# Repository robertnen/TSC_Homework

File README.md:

### Nenciu George-Robert 333CC

# TSC_Homework
## Schema pe scurt
<div align="center">
  
</div>
<br>

## Imaginea 3D 

<br>

# Conexiuni Hardware - Proiect ESP32-C6

## ESP32-C6-WROOM-1-N8 (Microcontroler Principal)
- Interfețe disponibile: SPI, I2C, UART, GPIO

---

## BME688 (Senzor Ambiental)
- Interfață: I2C  
- **Pini utilizați**:  
  - SDA → IO21  
  - SCL → IO22

---

## DS3231SN (Real-Time Clock)
- Interfață: I2C (partajat cu BME688)  
- **Pini utilizați**:  
  - SDA → IO21  
  - SCL → IO22  
  - INT_RTC → IO8  
  - 32KHZ → IO1  
  - RTC_RST → IO18

---

## Afișaj E-Ink (7.5 inch)
- Interfață: SPI  
- Rezoluție: 800 x 480 px  
- **Pini utilizați**:  
  - EPD_CS → IO10  
  - EPD_DC → IO5  
  - EPD_RST → IO23  
  - EPD_BUSY → IO3 *(partajat cu MISO)*  
  - MOSI, SCK *(partajate cu SD)*

---

## Modul SD Card
- Interfață: SPI  
- **Pini utilizați**:  
  - SS_SD → IO4  
  - MOSI → IO7  
  - MISO → IO2  
  - SCK → IO6

---

## Memorie Externă Flash (W25Q512JVEIQ, 64MB)
- Interfață: SPI  
- **Pini utilizați**:  
  - FLASH_CS → IO12  
  - MOSI, MISO, SCK *(partajate cu SD)*

---

## Interfață USB/SD
- Funcții: alimentare + date  
- **Pini utilizați**:  
  - USB_D+ → IO13  
  - USB_D- → IO12

---

## Butoane Boot și Reset
- **Pini utilizați**:  
  - IO/BOOT → IO9  
  - RESET → pin dedicat *(conform schemei)*

---

## Sistem de Alimentare și Management
- Baterie Li-Po: 3.7V, 2500mAh  
- **Module și pini**:
  - MCP73831 → încărcare prin USB-C  
  - MAX17048 → monitorizare baterie  
    - SDA → IO21  
    - SCL → IO22  
  - XC6220A331MR-G → 3.3V stabilizat

---

## Conector USB-C
- Funcții: alimentare principală și transfer de date  
- Protejat ESD

---

## Conector Qwiic / Stemma QT
- Interfață: I2C  
- **Pini utilizați**:
  - SDA → IO21  
  - SCL → IO22

<p>ESP32-C6 are un consum de energie optimizat pentru aplicații IoT. În modul activ, consumul variază în funcție de sarcină, dar poate fi redus semnificativ în modurile de repaus profund. De exemplu, în modul Deep Sleep, consumul poate fi de ordinul microamperilor, ceea ce permite o durată de viață extinsă a bateriei.</p>

### Notă privind erorile Airwire / Air Wire

În cadrul designului hardware, anumite erori de tip **Airwire** au fost acceptate intenționat în schema/PCB. Acestea reprezintă conexiuni logice nefinalizate în layout-ul plăcii, dar au fost tolerate în scopuri de testare, dezvoltare rapidă sau în situații unde conexiunile sunt realizate manual (ex: prin fire externe sau jumperi în faza de prototipare). 

Decizia de a le păstra a fost luată pentru a permite flexibilitate în modificări ulterioare și pentru a grăbi ciclul de iterație fără a compromite funcționalitatea de bază a sistemului.

## Alte considerații

<p>În proiectare, s-a ținut cont de recomandările din ghidul de design hardware pentru ESP32-C6 , asigurându-se că traseele PCB pentru interfața I2C sunt cât mai scurte și ecranate corespunzător pentru a minimiza interferențele. De asemenea, s-a acordat atenție alimentării corecte a senzorului BME680, conform specificațiilor acestuia.​

Pentru o integrare eficientă a componentelor și optimizarea performanței, s-au urmat recomandările din documentația oficială a ESP32-C6 și a componentelor asociate.</p>

| Componentă | Nr. bucăți | Nume material | Link către datasheet |
|---|---|---|---|
| EAGLE-LTSPICE_C0402 | 26 | Discrete Component | https://eu.mouser.com/datasheet/2/447/KEM_C1023_X7R_AUTO_SMD-3316698.pdf |
| ESP32_WROVER_AVX---SD0805S020S1R0_AVX_SD0805S020S1R0_0 | 2 | Discrete Component | https://eu.mouser.com/datasheet/2/40/AutoMLCCKAM-3216307.pdf |
| ESP32_WROVER_EAGLE-LTSPICE_R0402 | 22 | Discrete Component | https://eu.mouser.com/datasheet/2/54/cr-1858361.pdf |
| TP20R | 17 | Discrete Component | https://www.koaspeer.com/pdfs/RN73R.pdf |
| ESP32_WROVER_SPARKFUN-IC-POWER_SOT23-5 | 1 | Discrete Component | https://eu.mouser.com/datasheet/2/891/Espressif_Systems_ESP32_WROVER_E_L_0-3049094.pdf |
| ADAFRUIT_CHIP-LED0603 | 1 | Discrete Component | https://www.vishay.com/doc?82437 |
| ESP32_WROVER_BME680_PSON80P300X300X100-8N | 1 | Discrete Component | https://eu.mouser.com/datasheet/2/783/BST_BME680_DS001-1509608.pdf |
| ESP32C6_VARISTOR_CT/CN1812 | 1 | Discrete Component | https://product.tdk.com/system/files/dam/doc/product/protection/voltage/varistor_ctvs/data_sheet/75/db/ctvs_14/ct1210s14bautogx1.pdf |
| DIOC1608X36N | 6 | Discrete Component | https://eu.mouser.com/datasheet/2/802/1703143356438-3483895.pdf |
| SOT95P280X120-5N | 1 | Discrete Component | https://www.onsemi.com/PowerSolutions/product.do?id=MC74VHC1GT32P5T5G |
| CAPCP3225X100N | 1 | Discrete Component | https://eu.mouser.com/datasheet/2/18/2/CAP_CACFSBA1-3557832.pdf |
| RCL_CT3528 | 1 | Discrete Component | https://www.vishay.com/doc?20046 |
| ESP32_WROVER_SPARKFUN-DISCRETESEMI_SOT23-3 | 2 | Discrete Component | https://eu.mouser.com/datasheet/2/891/Espressif_Systems_ESP32_WROVER_E_L_0-3049094.pdf |
| SAMACSYS_PARTS_USB4110GFA | 1 | Discrete Component | https://eu.mouser.com/datasheet/2/837/GCT_USB4120-3159195.pdf |
| JST04_1MM_RA | 1 | Discrete Component | https://eu.mouser.com/datasheet/2/564/eCPT-3475515.pdf |
| SOIC127P1032X265-16N | 1 | Discrete Component | https://www.ti.com/lit/ug/sbou289/sbou289.pdf?ts=1664458800011&ref_url=https%253A%252F%252Fwww.ti.com%252Ftool%252FSURFACE-MOUNT-ADAPTER-EVM%253FkeyMatch%253D%2526tisearch%253Dsearch-everything%2526usecase%253Dhardware |
| XCVR_ESP32-C6-WROOM-1-N8 | 1 | Discrete Component | https://eu.mouser.com/datasheet/2/891/esp32_c6_datasheet_en-3304070.pdf |
| SOT95P280X145-6N | 1 | Discrete Component | https://eu.mouser.com/datasheet/2/414/DIV23-3532318.pdf |
| SOT95P280X125-5N | 1 | Discrete Component | https://eu.mouser.com/datasheet/2/414/DIV23-1551440.pdf |
| FH34SRJ24S05SH99 | 1 | Discrete Component | https://eu.mouser.com/datasheet/2/833/cherry_Rocker_SR_Round_EN-1275415.pdf |
| SON127P600X800X80-9N | 1 | Discrete Component | https://www.ti.com/lit/gpn/tps63710 |
| 16-soldermask | 1 | Steel | https://eu.mouser.com/datasheet/2/58/BPS-DAT-(BB3U)-Datasheet-1282462.pdf |

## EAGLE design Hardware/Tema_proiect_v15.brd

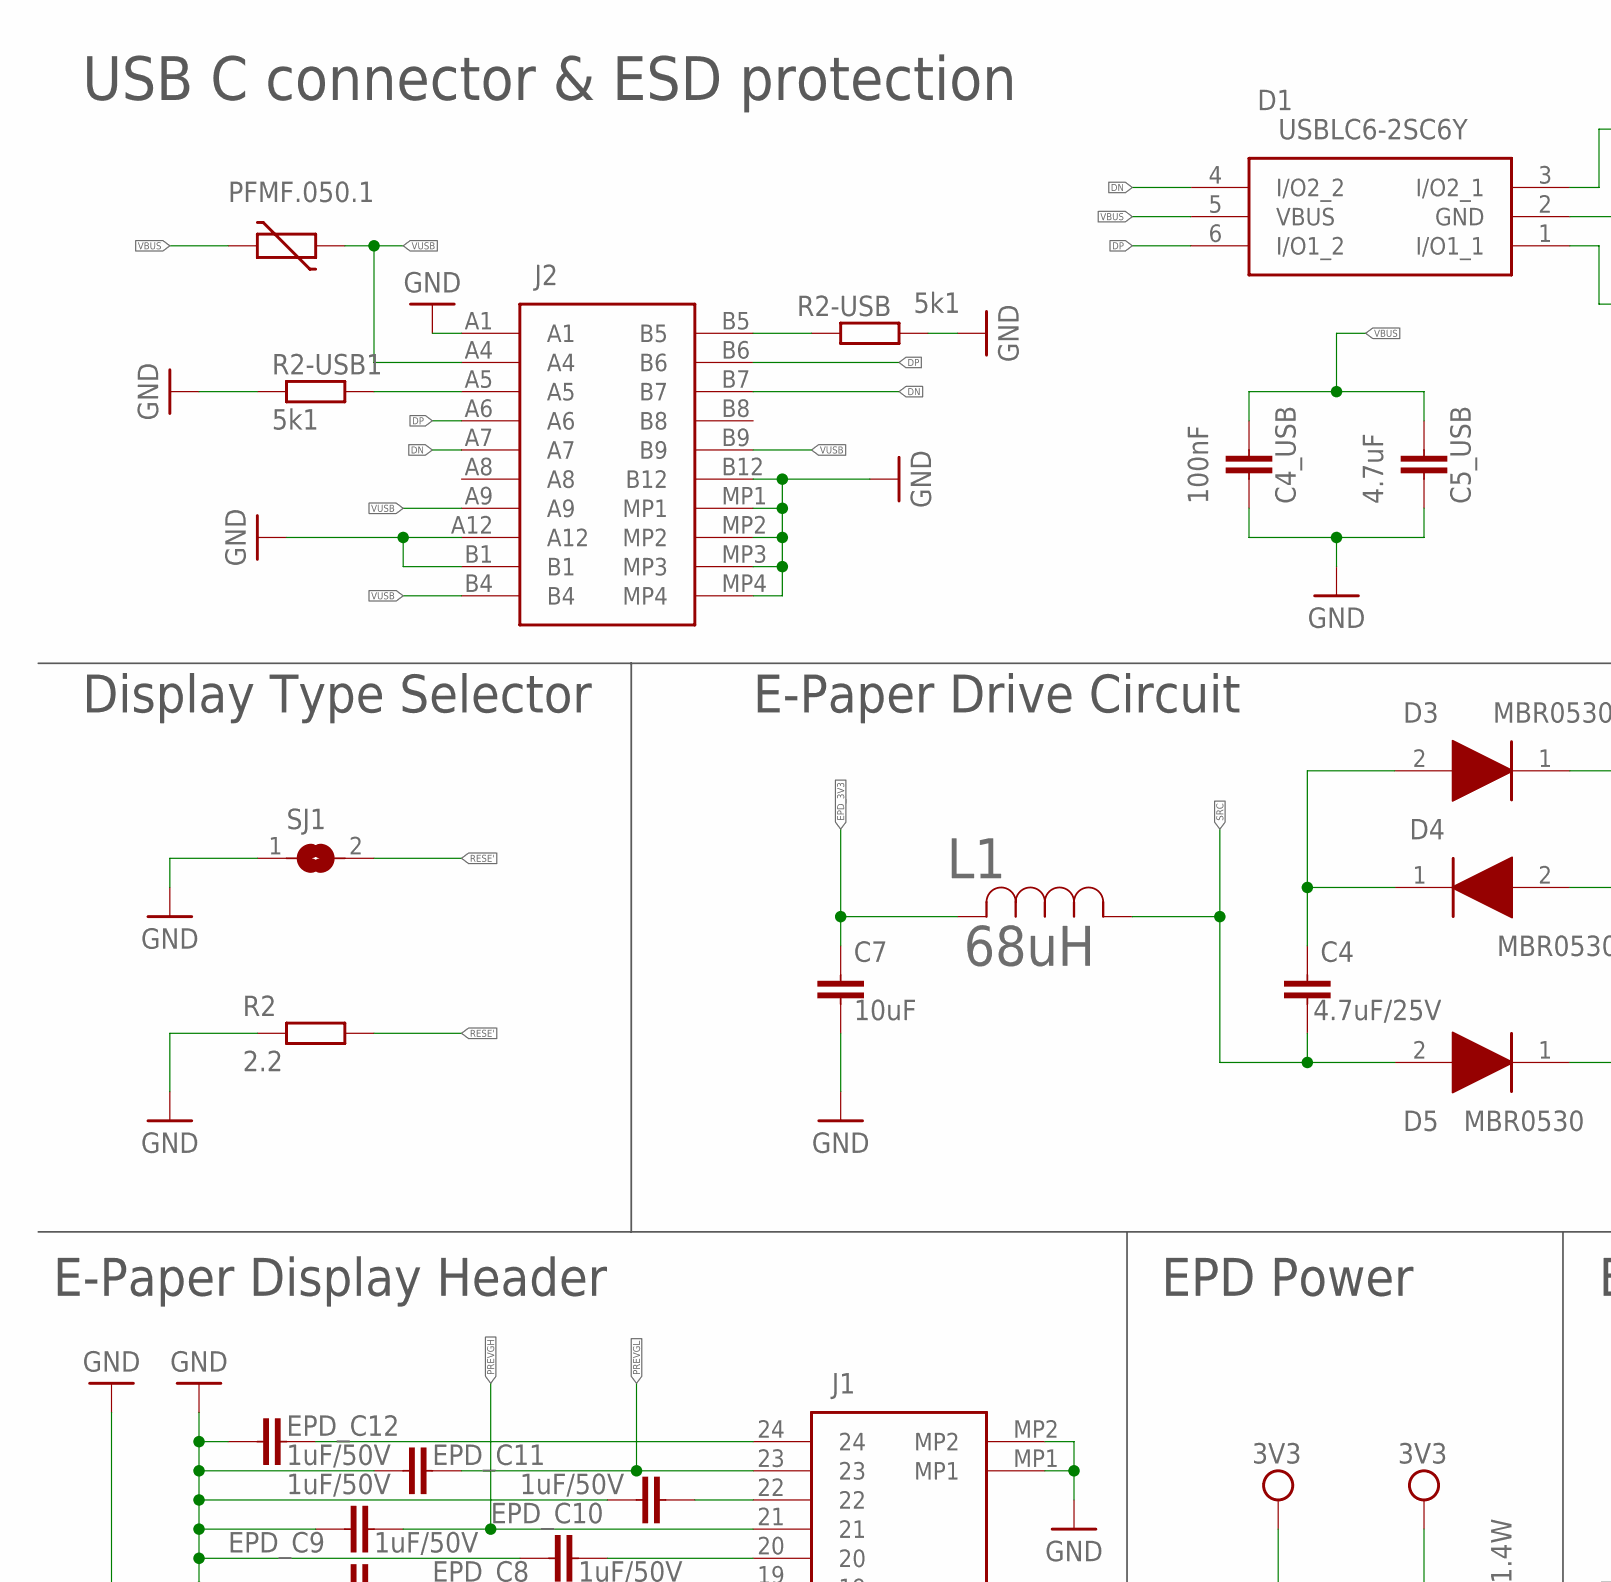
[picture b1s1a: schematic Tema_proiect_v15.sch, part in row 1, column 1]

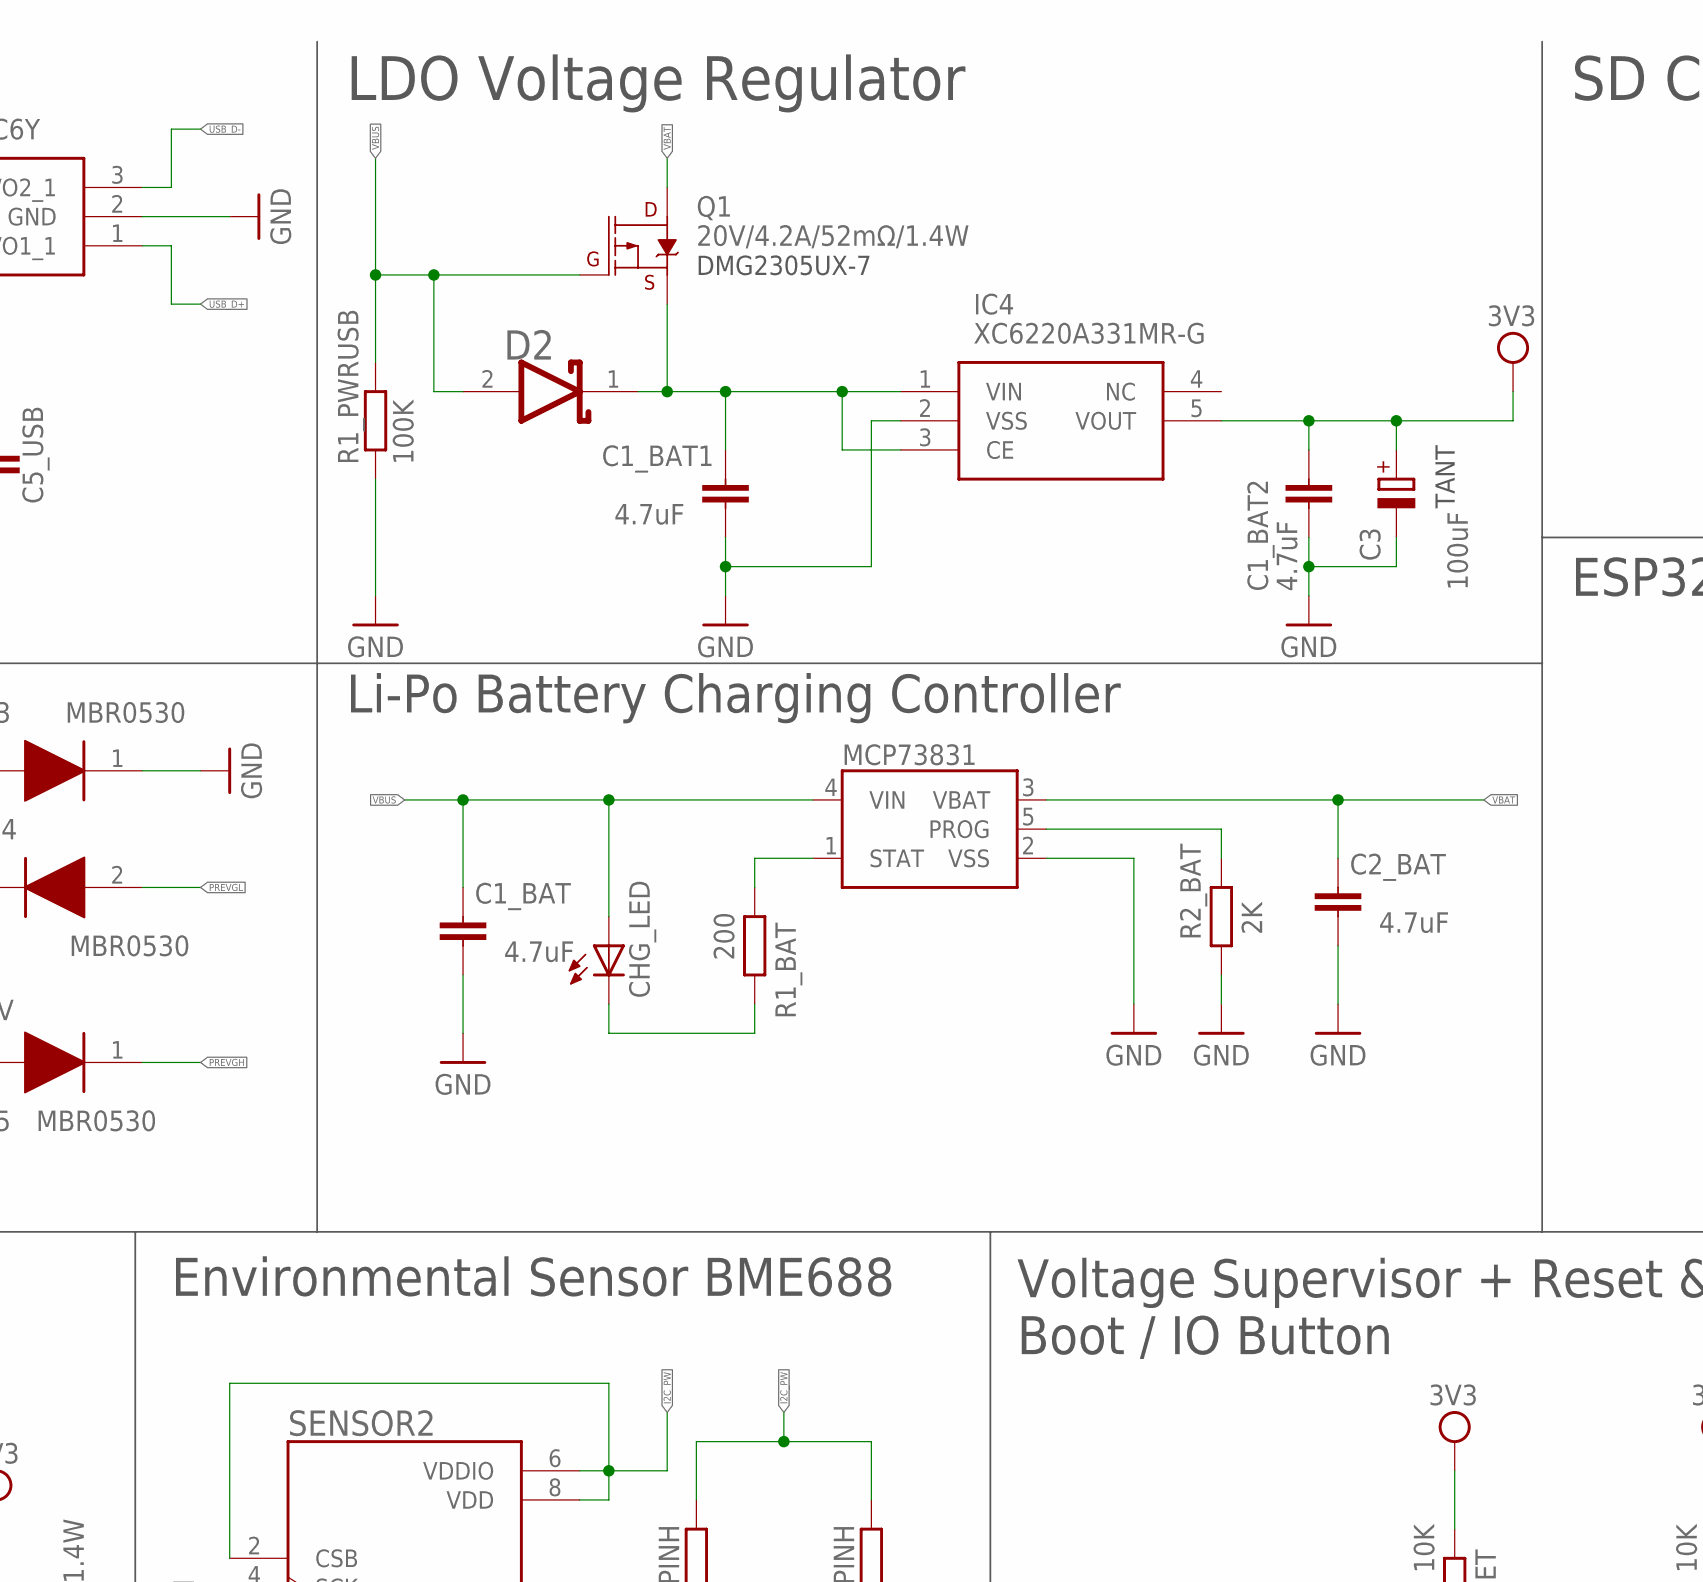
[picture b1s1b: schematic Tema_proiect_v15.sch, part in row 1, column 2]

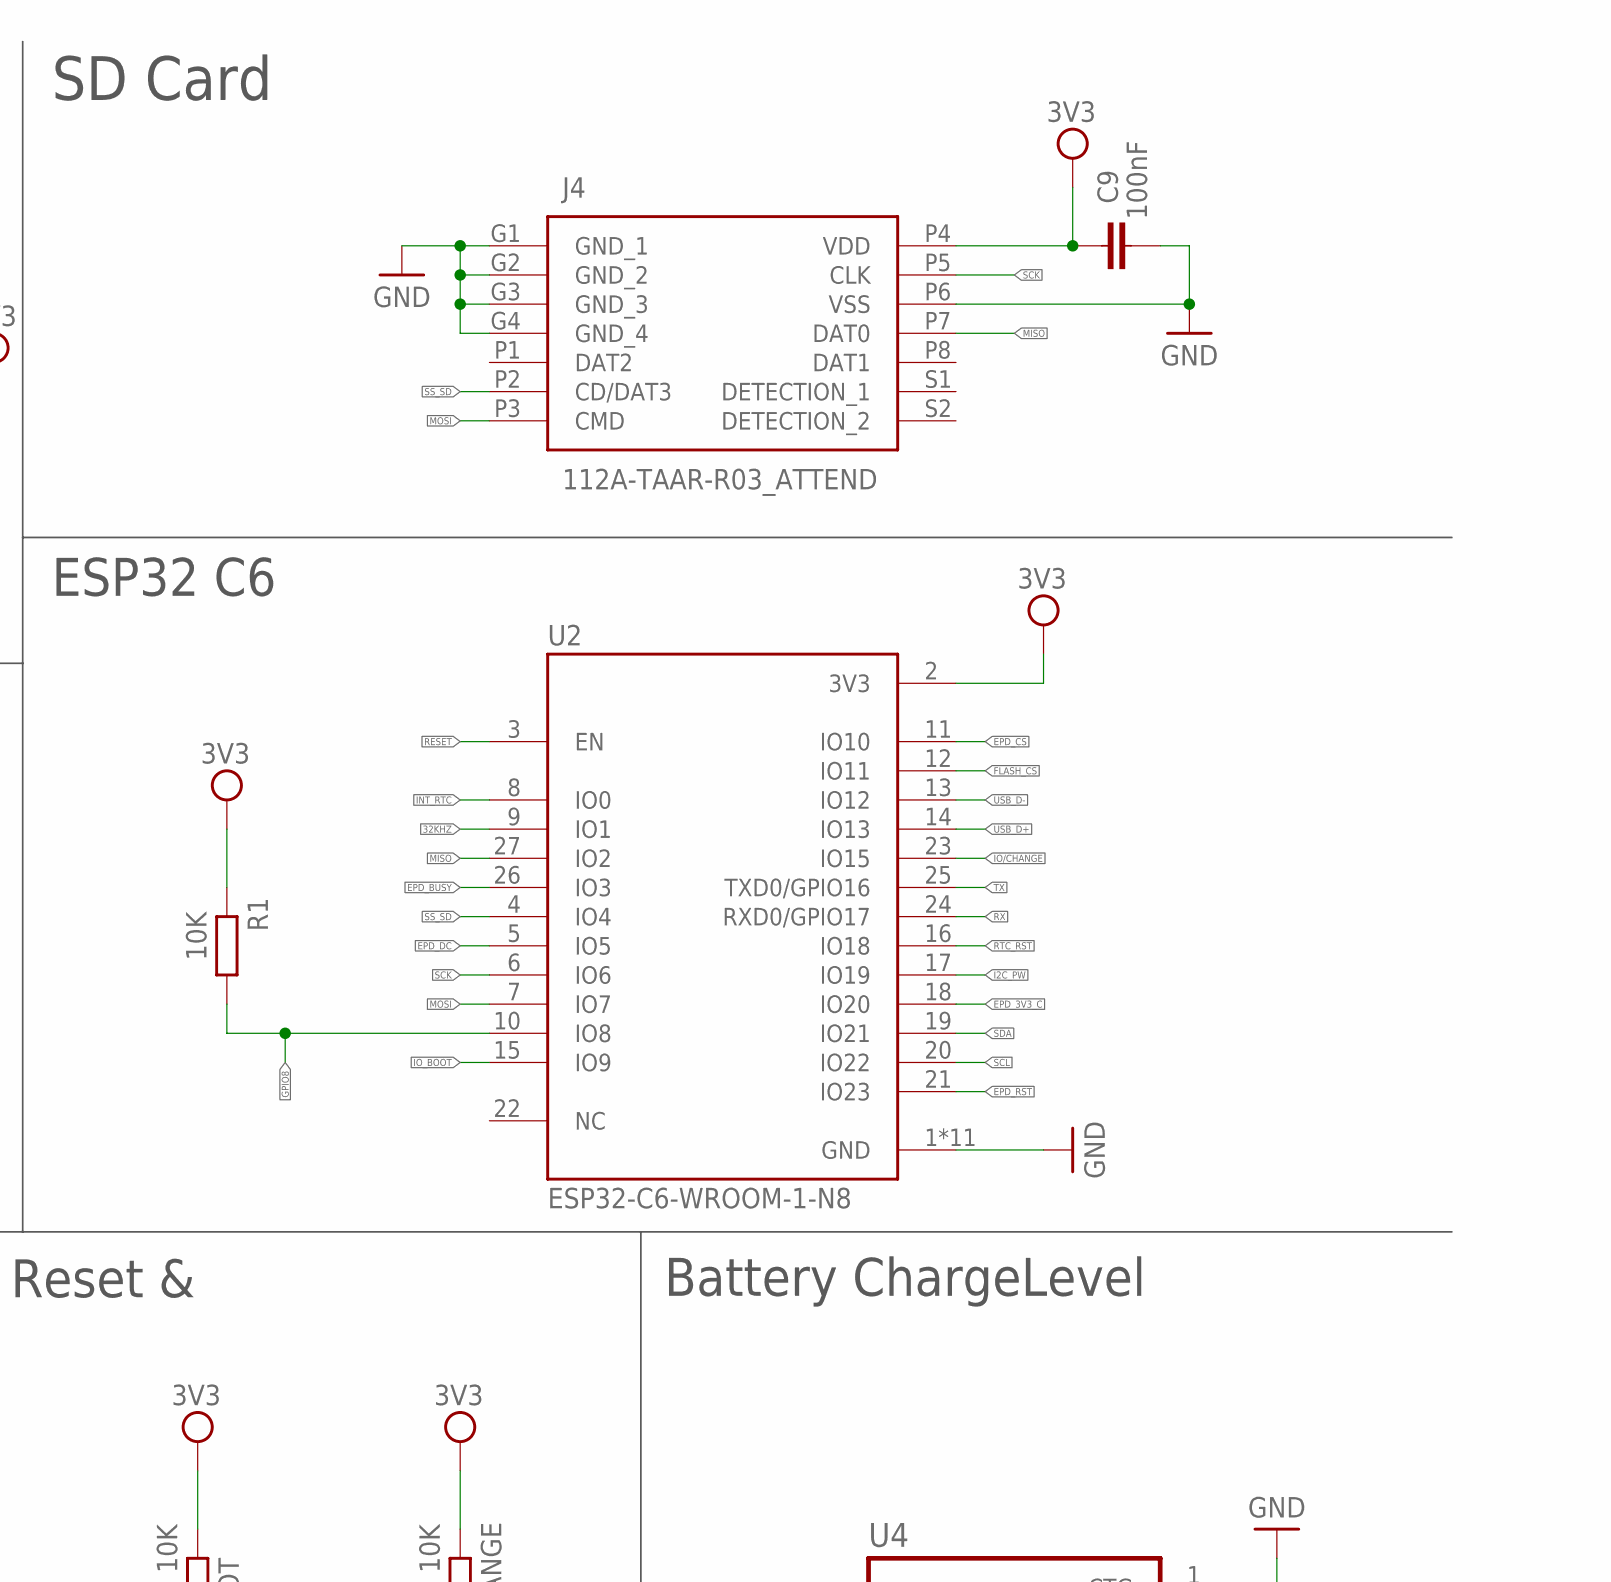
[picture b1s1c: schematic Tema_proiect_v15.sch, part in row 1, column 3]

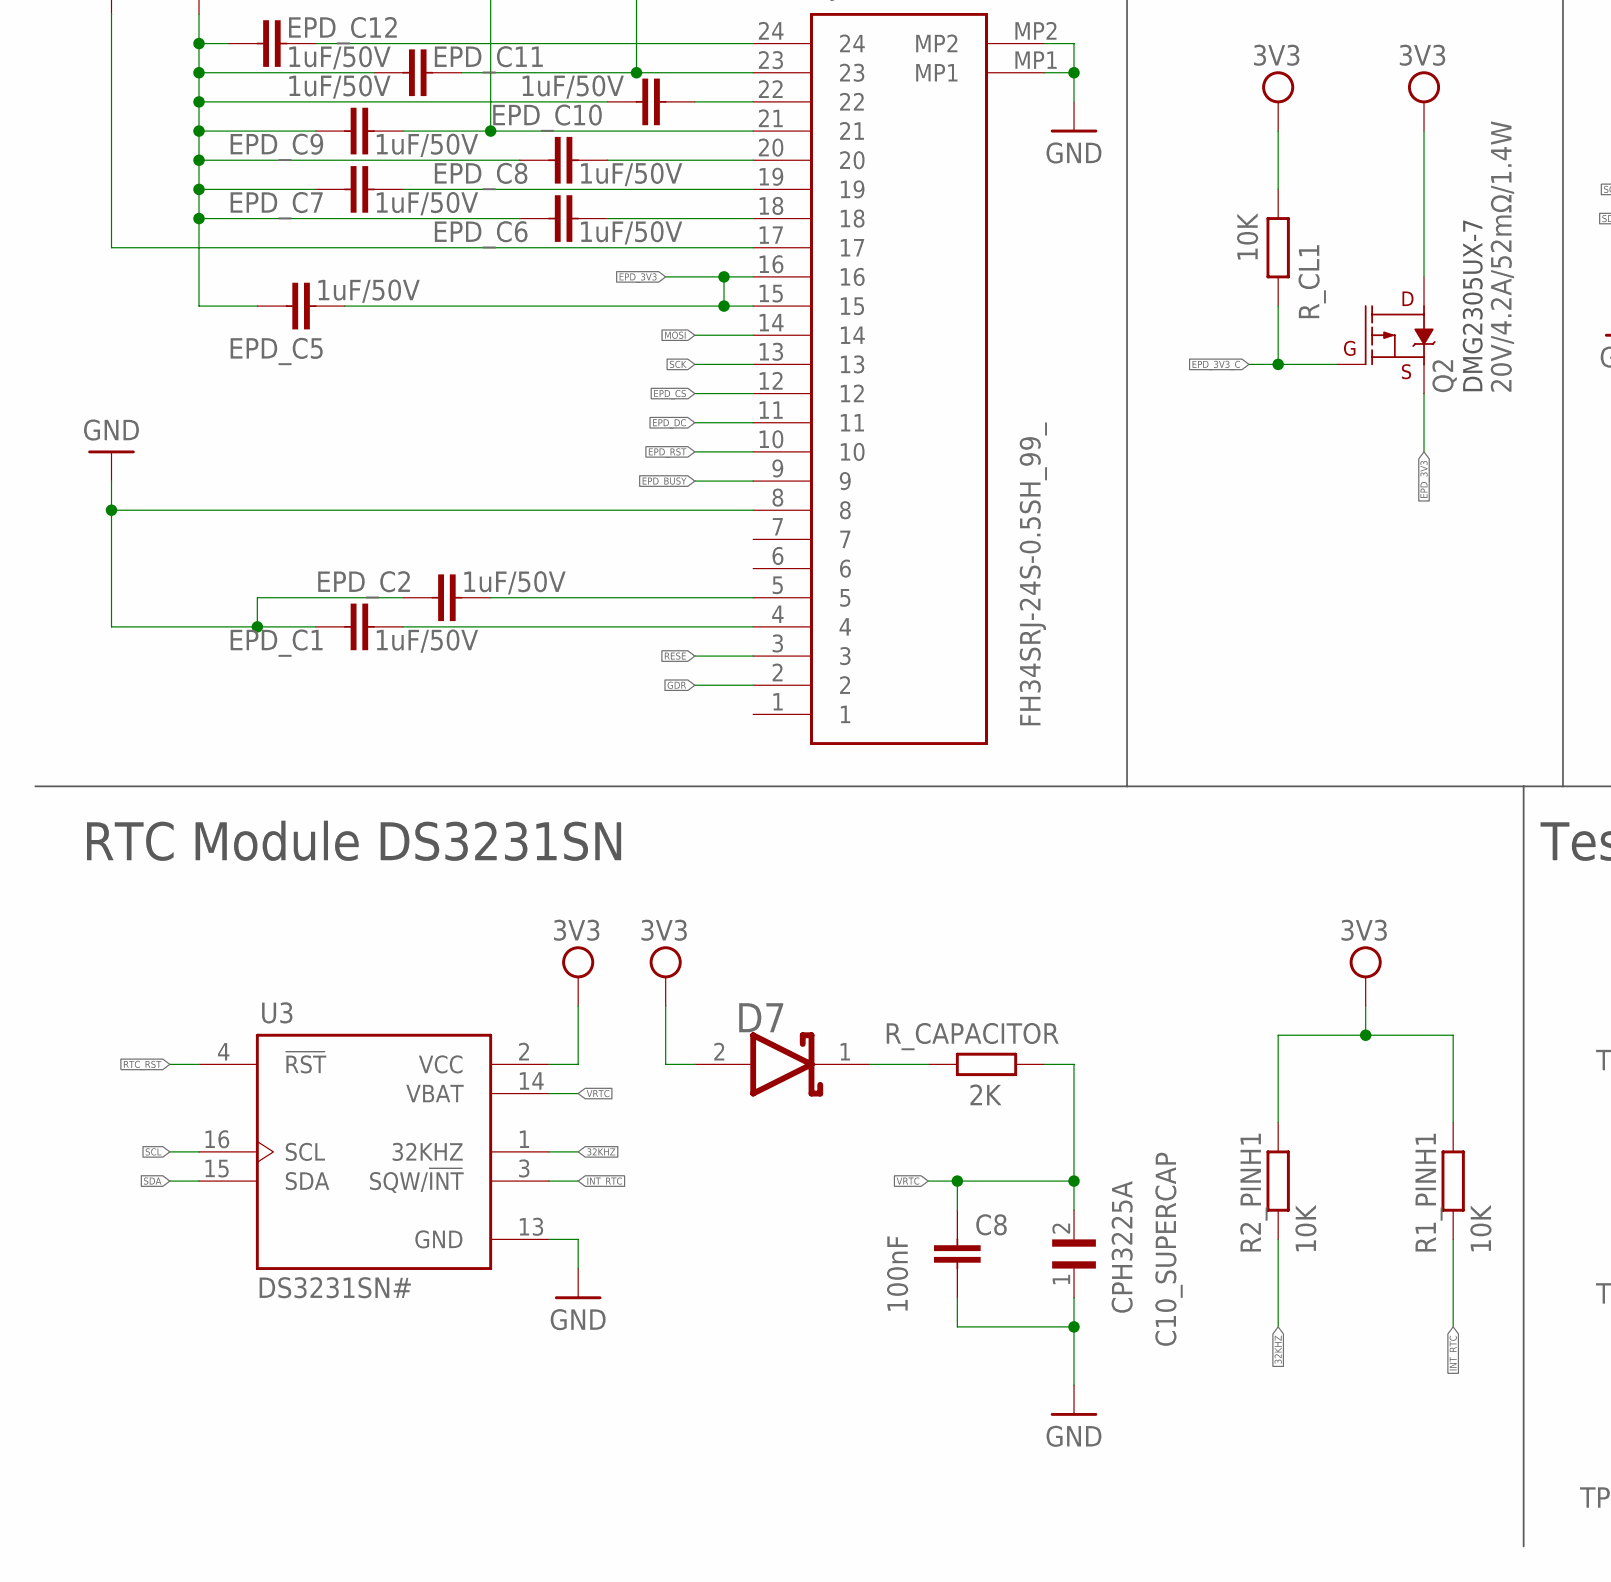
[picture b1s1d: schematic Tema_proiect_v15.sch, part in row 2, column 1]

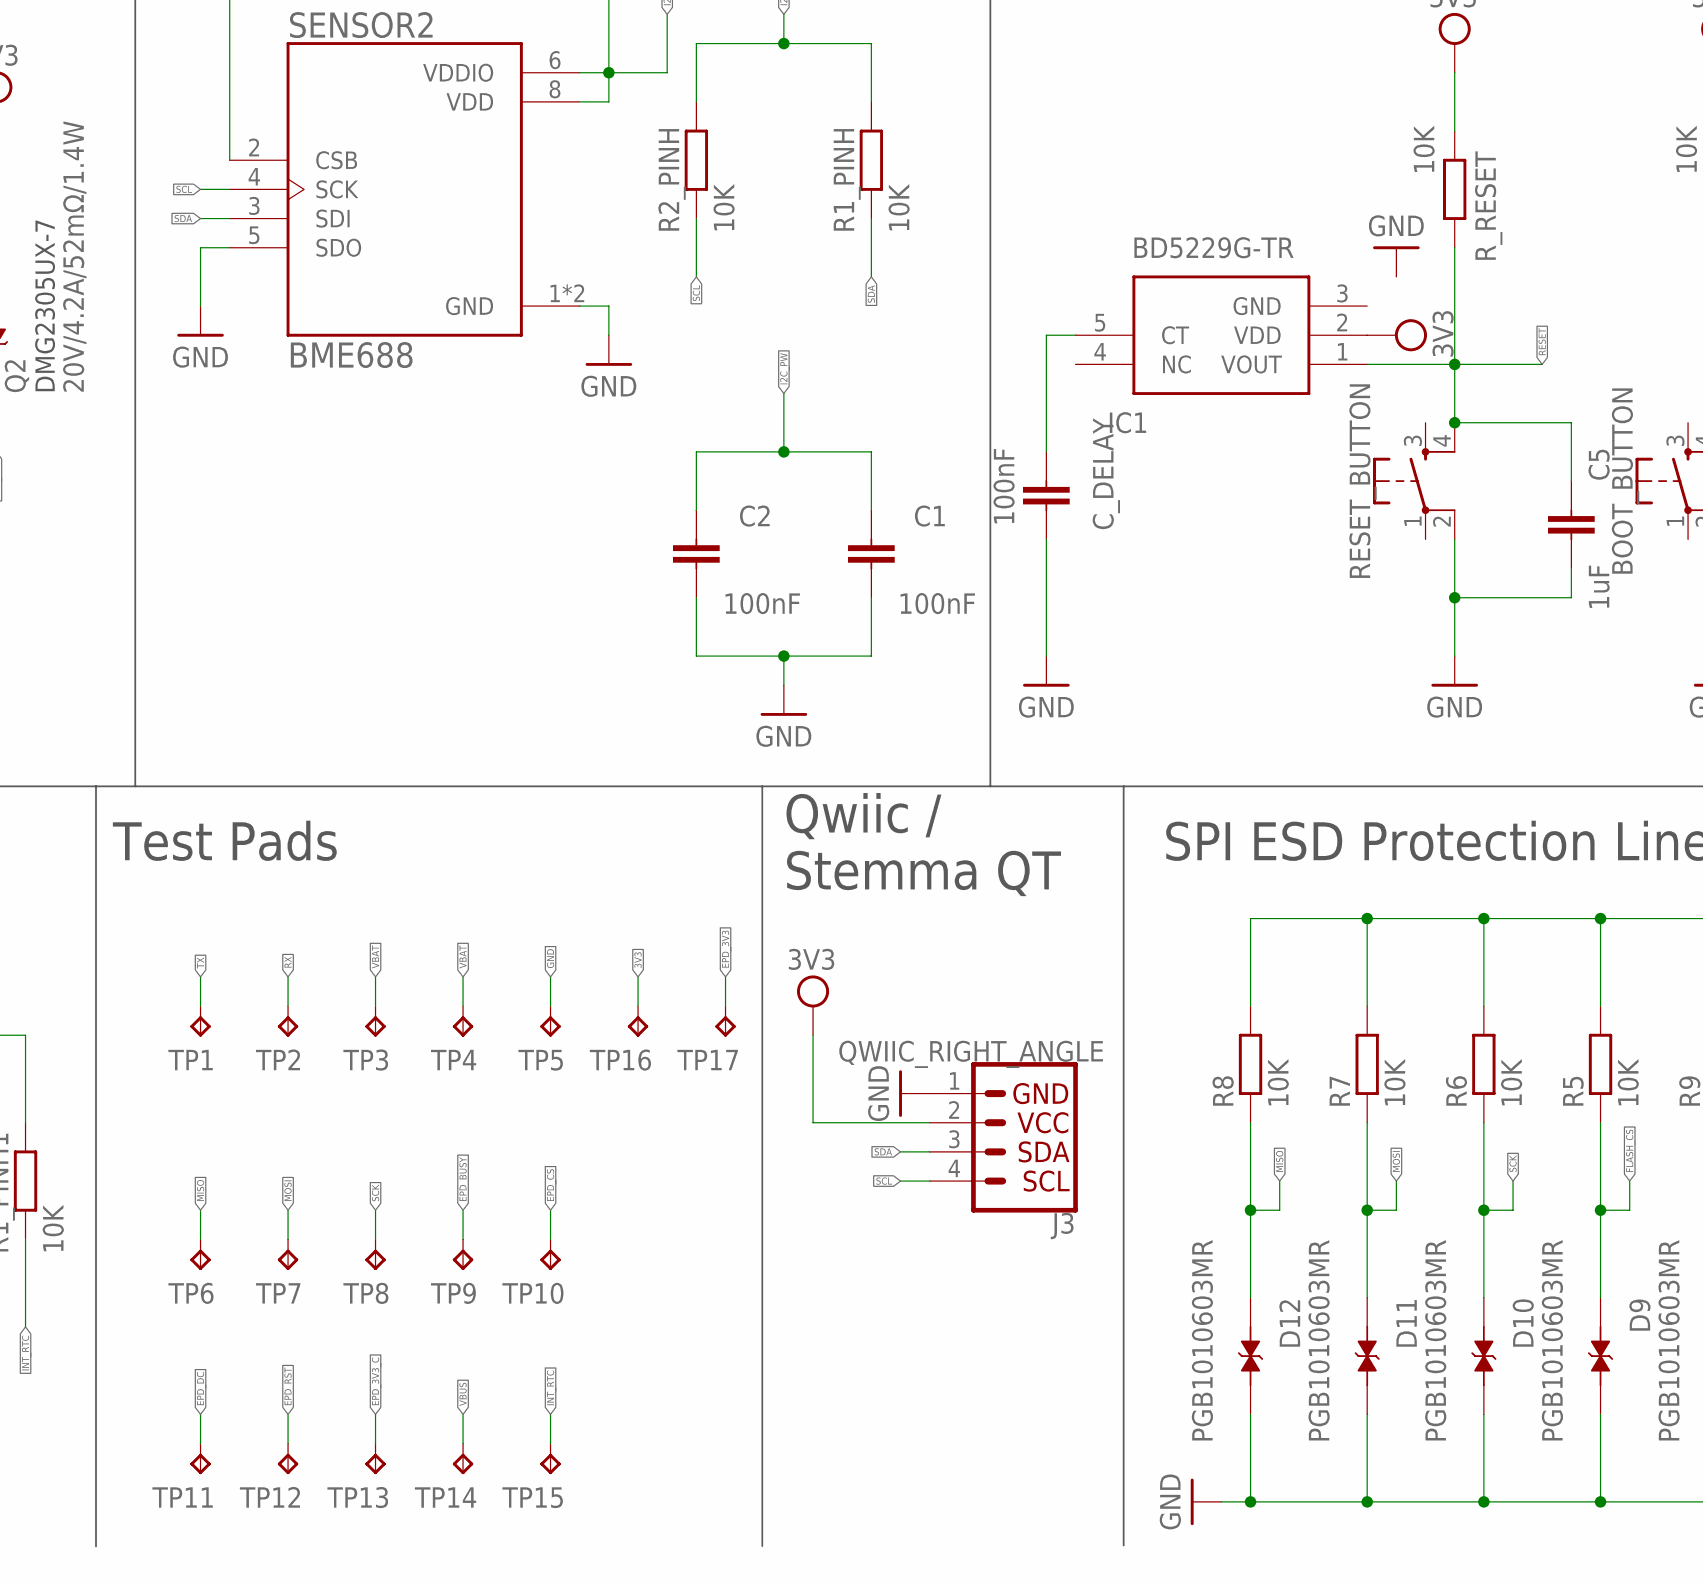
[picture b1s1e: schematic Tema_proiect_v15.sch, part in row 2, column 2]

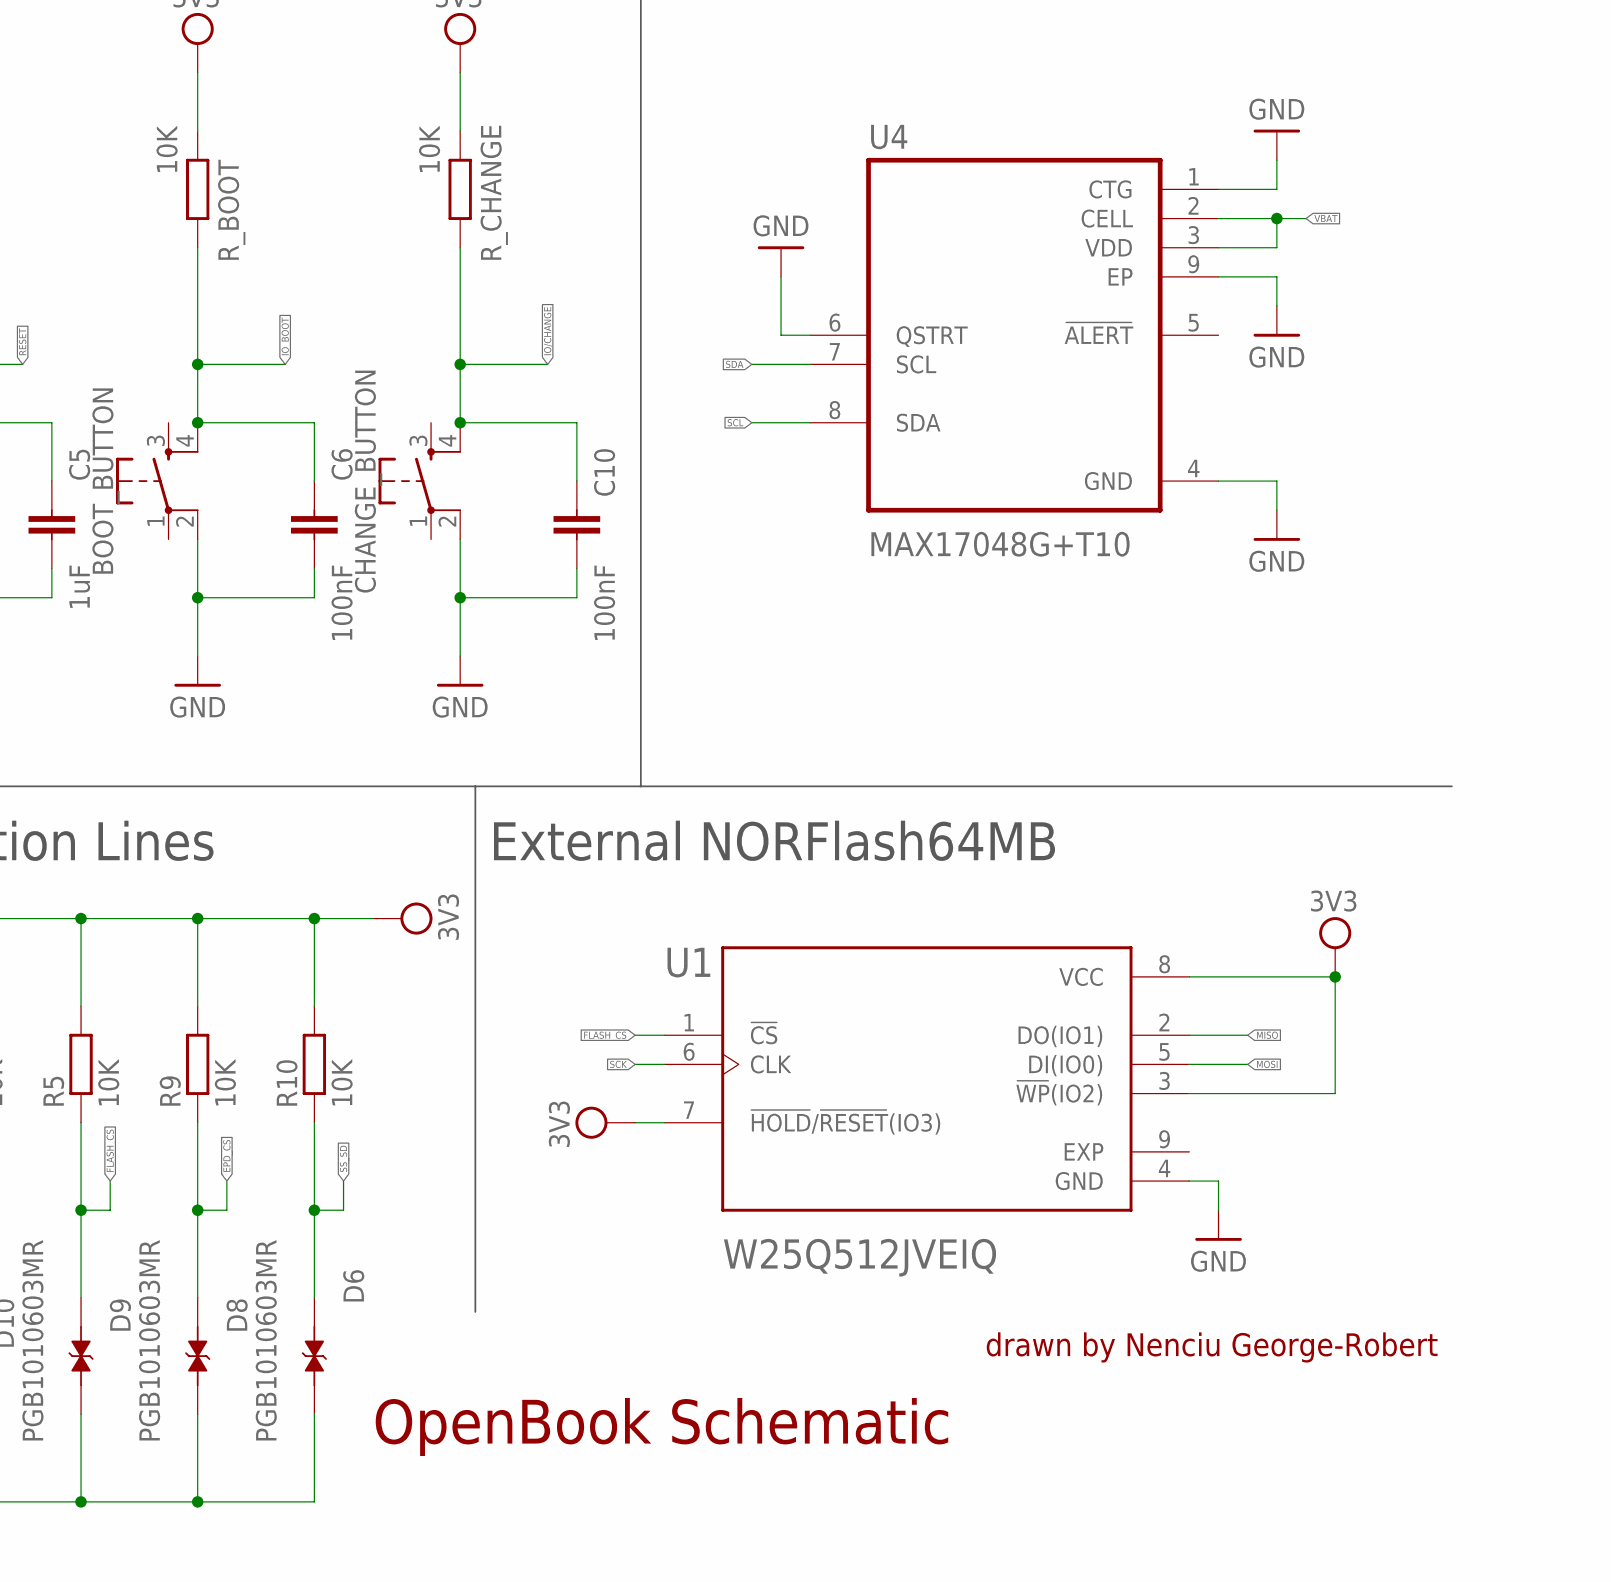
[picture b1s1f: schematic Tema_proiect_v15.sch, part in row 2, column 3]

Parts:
BOOT_BUTTON: BUTTON_CUSYOMV1; MYBUTTON
C1, C2, C4_USB, C6, C8, C9, C10: 100nF; EAGLE-LTSPICE_C0402
C1_BAT, C1_BAT1, C1_BAT2, C2_BAT, C5_USB: 4.7uF; EAGLE-LTSPICE_C0402
C3: 100uF; RCL_CT3528
C4: 4.7uF/25V; EAGLE-LTSPICE_C0402
C5: 1uF; EAGLE-LTSPICE_C0402
C7: 10uF; EAGLE-LTSPICE_C0402
C10_SUPERCAP: CPH3225A; CAPCP3225X100N
CHANGE_BUTTON: BUTTON_CUSYOMV1; MYBUTTON
CHG_LED: ADAFRUIT_LEDCHIP-LED0603; ADAFRUIT_CHIP-LED0603
C_DELAY: 100nF; EAGLE-LTSPICE_C0402
D1: USBLC6-2SC6Y; SOT95P280X145-6N
D2, D7: ESP32_WROVER_AVX---SD0805S020S1R0_AVX_SD0805S020S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; ESP32_WROVER_AVX---SD0805S020S1R0_AVX_SD0805S020S1R0_0
D3, D4, D5: MBR0530; SOD3716X135N
D6, D8, D9, D10, D11, D12: PGB1010603MR; DIOC1608X36N
EPD_C1, EPD_C2, EPD_C5, EPD_C6, EPD_C7, EPD_C8, EPD_C9, EPD_C10, EPD_C11, EPD_C12: 1uF/50V; EAGLE-LTSPICE_C0402
IC1: BD5229G-TR; SOT95P280X125-5N
IC4: XC6220A331MR-G; SOT95P280X120-5N
J1: FH34SRJ-24S-0.5SH_99_; FH34SRJ24S05SH99
J2: SAMACSYS_PARTS_USB4110-GF-A; SAMACSYS_PARTS_USB4110GFA
J3: QWIIC_RIGHT_ANGLE; JST04_1MM_RA
J4: 112A-TAAR-R03_ATTEND; 112ATAARR03ATTEND
L1: 68uH; IND_4828-WE-TPC_WRE
MCP73831: ESP32_WROVER_SPARKFUN-IC-POWER_MCP73831; ESP32_WROVER_SPARKFUN-IC-POWER_SOT23-5
PFMF.050.1: ESP32C6_VARISTORCN1812; ESP32C6_VARISTOR_CT/CN1812
Q1, Q2: 20V/4.2A/52mΩ/1.4W; ESP32_WROVER_SPARKFUN-DISCRETESEMI_SOT23-3
R1, R1_PINH, R1_PINH1, R2_PINH, R2_PINH1, R5, R6, R7, R8, R9, R10: 10K; ESP32_WROVER_EAGLE-LTSPICE_R0402
R1_BAT: 200; ESP32_WROVER_EAGLE-LTSPICE_R0402
R1_PWRUSB: 100K; ESP32_WROVER_EAGLE-LTSPICE_R0402
R2: 2.2; ESP32_WROVER_EAGLE-LTSPICE_R0402
R2-USB, R2-USB1: 5k1; ESP32_WROVER_EAGLE-LTSPICE_R0402
R2_BAT: 2K; ESP32_WROVER_EAGLE-LTSPICE_R0402
RESET_BUTTON: BUTTON_CUSYOMV1; MYBUTTON
R_BOOT: 10K; ESP32_WROVER_EAGLE-LTSPICE_R0402
R_CAPACITOR: 2K; ESP32_WROVER_EAGLE-LTSPICE_R0402
R_CHANGE: 10K; ESP32_WROVER_EAGLE-LTSPICE_R0402
R_CL1: 10K; ESP32_WROVER_EAGLE-LTSPICE_R0402
R_RESET: 10K; ESP32_WROVER_EAGLE-LTSPICE_R0402
SENSOR2: BME688; ESP32_WROVER_BME680_PSON80P300X300X100-8N
SJ1: SJ
TP1, TP2, TP3, TP4, TP5, TP6, TP7, TP8, TP9, TP10, TP11, TP12, TP13, TP14, TP15, TP16, TP17: TPTP20R; TP20R
U1: W25Q512JVEIQ; SON127P600X800X80-9N
U2: ESP32-C6-WROOM-1-N8; XCVR_ESP32-C6-WROOM-1-N8
U3: DS3231SN#; SOIC127P1032X265-16N
U4: MAX17048G+T10; SON50P200X200X80-9N

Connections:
3V3: C1_BAT2.1, C3.+, C9.1, D7.2 (ANODE), IC1.2 (VDD), IC4.5 (VOUT), J3.2, J4.P4 (VDD), Q2.3 (D), R1.2, R1_PINH1.2, R2_PINH1.2, R5.2, R6.2, R7.2, R8.2, R9.2, R10.2, R_BOOT.2, R_CHANGE.2, R_CL1.2, R_RESET.2, TP16.TP, U1.3 (!WP!(IO2)), U1.7 (!HOLD!/!RESET!(IO3)), U1.8 (VCC), U2.2 (3V3), U3.2 (VCC)
32KHZ: R2_PINH1.1, U2.9 (IO1), U3.1 (32KHZ)
DN: D1.4 (I/O2_2), J2.A7, J2.B7
DP: D1.6 (I/O1_2), J2.A6, J2.B6
EPD_3V3: C7.1, L1.2, Q2.2 (S), TP17.TP
EPD_3V3_C: TP13.TP, U2.18 (IO20)
EPD_BUSY: J1.9, TP9.TP, U2.26 (IO3)
EPD_CS: D8.1, J1.12, R9.1, TP10.TP, U2.11 (IO10)
EPD_DC: J1.11, TP11.TP, U2.5 (IO5)
EPD_RST: J1.10, TP12.TP, U2.21 (IO23)
FLASH_CS: D9.1, R5.1, U1.1 (!CS), U2.12 (IO11)
GDR: J1.2
GND: BOOT_BUTTON.2, C1.2, C1_BAT.2, C1_BAT1.2, C1_BAT2.2, C2.2, C2_BAT.2, C3.-, C4_USB.2, C5.2, C5_USB.2, C6.2, C7.2, C8.2, C9.2, C10.2, C10_SUPERCAP.1, CHANGE_BUTTON.2, C_DELAY.2, D1.2 (GND), D3.1 (K), D6.2, D8.2, D9.2, D10.2, D11.2, D12.2, EPD_C1.1, EPD_C2.1, EPD_C5.1, EPD_C6.1, EPD_C7.1, EPD_C8.1, EPD_C9.1, EPD_C10.1, EPD_C11.1, EPD_C12.1, IC4.2 (VSS), J1.8, J1.17, J1.MP1, J1.MP2, J2.A1, J2.A12, J2.B1, J2.B12, J2.MP1, J2.MP2, J2.MP3, J2.MP4, J3.1, J4.G1 (GND_1), J4.G2 (GND_2), J4.G3 (GND_3), J4.G4 (GND_4), J4.P6 (VSS), MCP73831.2 (VSS), R1_PWRUSB.1, R2.1, R2-USB.2, R2-USB1.1, R2_BAT.2, RESET_BUTTON.2, SENSOR2.1 (GND), SENSOR2.5 (SDO), SENSOR2.7 (GND), SJ1.1, TP5.TP, U1.4 (GND), U2.1 (GND), U2.28 (GND), U2.29_1 (GND), U2.29_2 (GND), U2.29_3 (GND), U2.29_4 (GND), U2.29_5 (GND), U2.29_6 (GND), U2.29_7 (GND), U2.29_8 (GND), U2.29_9 (GND), U3.13 (GND), U4.1 (CTG), U4.4 (GND), U4.6 (QSTRT), U4.9 (EP)
GPIO8: R1.1, U2.10 (IO8)
I2C_PW: U2.17 (IO19)
INT_RTC: R1_PINH1.1, TP15.TP, U2.8 (IO0), U3.3 (SQW/!INT)
IO/CHANGE: U2.23 (IO15)
IO_BOOT: U2.15 (IO9)
MISO: D12.1, J4.P7 (DAT0), R8.1, TP6.TP, U1.2 (DO(IO1)), U2.27 (IO2)
MOSI: D11.1, J1.14, J4.P3 (CMD), R7.1, TP7.TP, U1.5 (DI(IO0)), U2.7 (IO7)
unnamed: J2.A5, R2-USB1.2
unnamed: J2.B5, R2-USB.1
unnamed: C1_BAT1.1, D2.1 (CATHODE), IC4.1 (VIN), IC4.3 (CE), Q1.2 (S)
unnamed: C4.1, D3.2 (A), D4.1 (K)
unnamed: MCP73831.1 (STAT), R1_BAT.2
unnamed: CHG_LED.C, R1_BAT.1
unnamed: MCP73831.5 (PROG), R2_BAT.1
unnamed: EPD_C12.2, J1.24
unnamed: EPD_C11.2, J1.23
unnamed: EPD_C10.2, J1.22
unnamed: EPD_C9.2, J1.21
unnamed: EPD_C8.2, J1.20
unnamed: EPD_C7.2, J1.19
unnamed: EPD_C6.2, J1.18
unnamed: EPD_C5.2, J1.15, J1.16
unnamed: EPD_C2.2, J1.5
unnamed: EPD_C1.2, J1.4
unnamed: Q2.1 (G), R_CL1.1
unnamed: R1_PINH.2, R2_PINH.2
unnamed: SENSOR2.2 (CSB), SENSOR2.6 (VDDIO), SENSOR2.8 (VDD)
unnamed: C1.1, C2.1
unnamed: C5.1, IC1.1 (VOUT), RESET_BUTTON.4, R_RESET.1
unnamed: BOOT_BUTTON.4, C6.1, R_BOOT.1
unnamed: C10.1, CHANGE_BUTTON.4, R_CHANGE.1
unnamed: C_DELAY.1, IC1.5 (CT)
unnamed: D7.1 (CATHODE), R_CAPACITOR.2
unnamed: C8.1, C10_SUPERCAP.2, R_CAPACITOR.1
PREVGH: D5.1 (K)
PREVGL: D4.2 (A)
RESE: J1.3
RESE': R2.2, SJ1.2
RESET: U2.3 (EN)
RTC_RST: U2.16 (IO18), U3.4 (!RST)
RX: TP2.TP, U2.24 (RXD0/GPIO17)
SCK: D10.1, J1.13, J4.P5 (CLK), R6.1, TP8.TP, U1.6 (CLK), U2.6 (IO6)
SCL: J3.4, R2_PINH.1, SENSOR2.4 (SCK), U2.20 (IO22), U3.16 (SCL), U4.8 (SDA)
SDA: J3.3, R1_PINH.1, SENSOR2.3 (SDI), U2.19 (IO21), U3.15 (SDA), U4.7 (SCL)
SRC: C4.2, D5.2 (A), L1.1
SS_SD: D6.1, J4.P2 (CD/DAT3), R10.1, U2.4 (IO4)
TX: TP1.TP, U2.25 (TXD0/GPIO16)
USB_D+: D1.1 (I/O1_1), U2.14 (IO13)
USB_D-: D1.3 (I/O2_1), U2.13 (IO12)
VBAT: C2_BAT.1, MCP73831.3 (VBAT), Q1.3 (D), TP3.TP, TP4.TP, U4.2 (CELL), U4.3 (VDD)
VBUS: C1_BAT.1, C4_USB.1, C5_USB.1, CHG_LED.A, D1.5 (VBUS), D2.2 (ANODE), MCP73831.4 (VIN), PFMF.050.1.2, Q1.1 (G), R1_PWRUSB.2, TP14.TP
VRTC: U3.14 (VBAT)
VUSB: J2.A4, J2.A9, J2.B4, J2.B9, PFMF.050.1.1

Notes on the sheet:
USB C connector & ESD protection
DMG2305UX-7
TANT
LDO Voltage Regulator
SD Card
Display Type Selector
E-Paper Drive Circuit
Li-Po Battery Charging Controller
ESP32 C6
E-Paper Display Header
EPD Power
Environmental Sensor BME688
Voltage Supervisor + Reset & Boot / IO Button
Battery ChargeLevel
RTC Module DS3231SN
Test Pads
Qwiic / Stemma QT
SPI ESD Protection Lines
External NORFlash64MB
OpenBook Schematic
drawn by Nenciu George-Robert

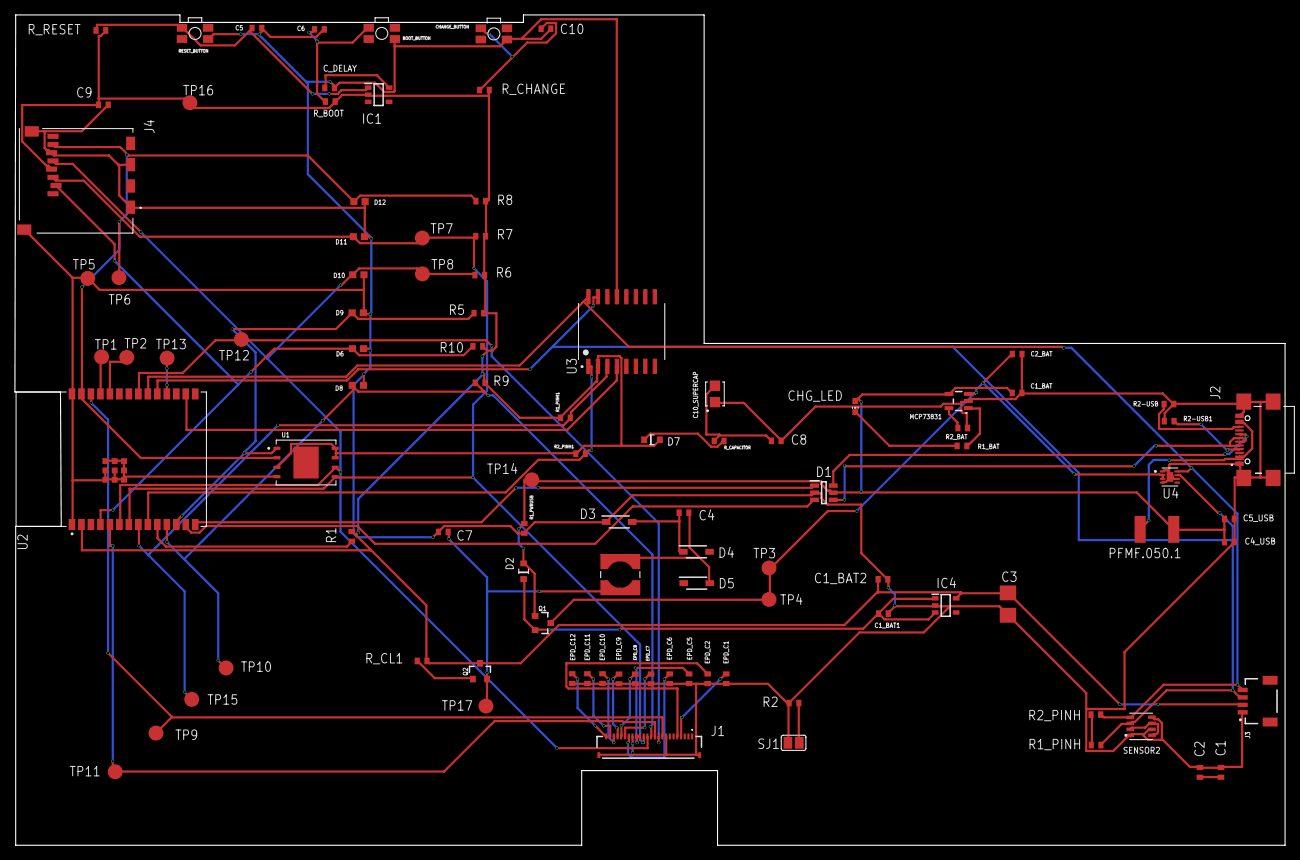
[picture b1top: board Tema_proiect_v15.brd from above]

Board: 2 copper layers, 170.1 x 111.2 mm, 100 parts (0 on the bottom side), 57 nets.

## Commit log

2025-04-04 Added homework
2025-04-04 Create LICENSE

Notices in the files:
parts and their libraries:
COPYRIGHT: Copyright (C) 2024 Ultra Librarian. All rights reserved.
